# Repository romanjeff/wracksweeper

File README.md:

We are a Capstone team working with the Portland State University NEAR lab, under advisement by Dr. Martin
Siderius, and this repo is for the necessary files to implement or reference tha customizations we have done
to the AUV owned by the NEAR lab for academic research purposes. 

Our AUV is a Riptide Systems MP1 Mk.II, managed by a Beaglebone Black running MOOS-IvP (http://www.moos-ivp.org).

The project goal is to have full side-scan sonar capabilities, an emergency asset recovery tracking beacon, 
rechargeable power supply, and long-range wireless communications allowing us to check on the AUV's status,
give it new mission parameters, or toggle sonar functions without recovery and relaunch. Added features are
modular and removable to restore original state to the AUV.

Our sonar system is an Imagenex OEM side-scan module, and our wireless communications are done over LoRa at 
915 MHz using the Adafruit Feather M0 with HopeRF RFM95 transceiver modules. 

This project has been conducted at Portland State University by a team consisting of:

Drew Wendebrn, Matthew Moore, Patrick Hawn - Mechanical Engineering.  

Roman Minko, Adel Alkharraz - Sonar Interface Software.  

Colton Bruce - Beacon and RF link characterization.  

Jeff Roman - Communications Software.  

Jens Evens, Grace Semerdjian - Power System.  

http://www.wracksweeper.com

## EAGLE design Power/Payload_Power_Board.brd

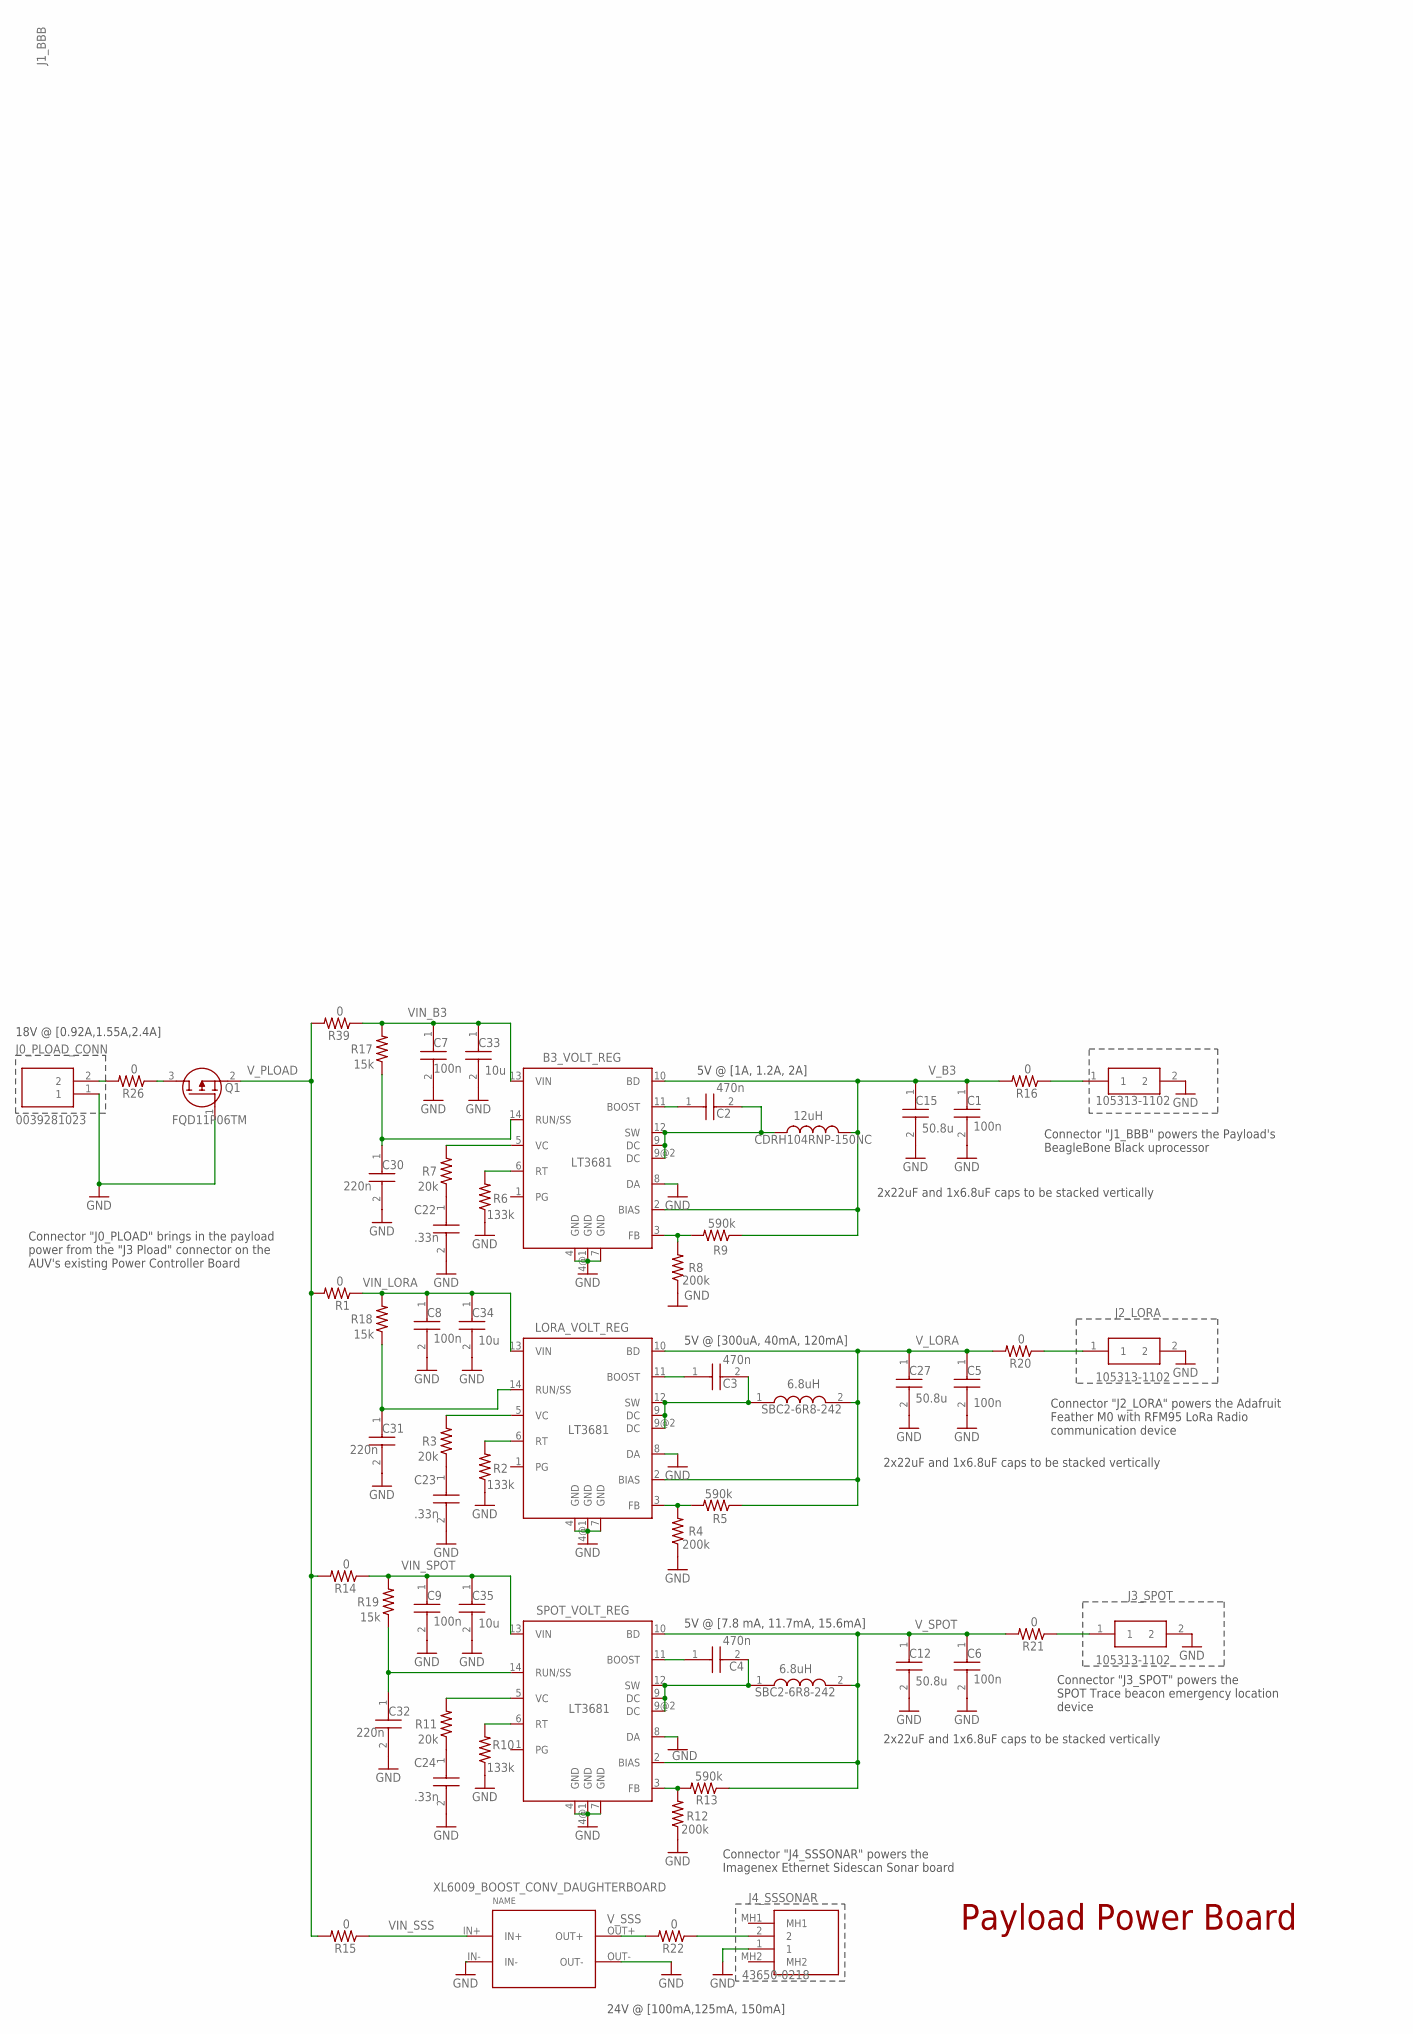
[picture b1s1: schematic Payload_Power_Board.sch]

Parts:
B3_VOLT_REG: LT3681; DFN14-4X3DE
C1, C5, C6, C7, C8, C9: 100n; CAPC1608X90N
C2, C3, C4: 470n; CAPC1608X90N
C12, C15, C27: 50.8u; CAPC3225X279N
C22, C23, C24: .33n; CAPC2012X140N
C30, C31, C32: 220n; CAPC2012X140N
C33, C34, C35: 10u; CAPC5750X279N
INDUCTOR_3: CDRH104RNP-150NC; INDPM102100X400N
J0_PLOAD_CONN: 0039281023; SHDR2W145P0X550_1X2_960X540X13
J1_BBB, J2_LORA, J3_SPOT: 105313-1102; 1053131102
J4_SSSONAR: 43650-0218; 436500218
L4, L5: SBC2-6R8-242; SBC26R8242
LORA_VOLT_REG: LT3681; DFN14-4X3DE
Q1: FQD11P06TM; DPAK3-CASE-369AS
R1, R14, R15, R16, R20, R21, R22, R26, R39: 0; 0207/2V; MPN RC0805FR-0710KL
R2, R6, R10: 133k; R0603
R3, R7, R11: 20k; R0603
R4, R8, R12: 200k; R0603
R5, R9, R13: 590k; R0603
R17, R18, R19: 15k; R0603
SPOT_VOLT_REG: LT3681; DFN14-4X3DE
XL6009_BOOST_CONV_DAUGHTERBOARD: XL6009; CP8-ADJ

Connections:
CBOOST_B3: B3_VOLT_REG.11 (BOOST), C2.1
CBOOST_LORA: C3.1, LORA_VOLT_REG.11 (BOOST)
CBOOST_SPOT: C4.1, SPOT_VOLT_REG.11 (BOOST)
FB_B3: B3_VOLT_REG.3 (FB), R8.2, R9.2
FB_LORA: LORA_VOLT_REG.3 (FB), R4.2, R5.2
FB_SPOT: R12.2, R13.2, SPOT_VOLT_REG.3 (FB)
GND: B3_VOLT_REG.4 (GND), B3_VOLT_REG.4@1 (GND), B3_VOLT_REG.7 (GND), B3_VOLT_REG.8 (DA), C1.2, C5.2, C6.2, C7.2, C8.2, C9.2, C12.2, C15.2, C22.2, C23.2, C24.2, C27.2, C30.2, C31.2, C32.2, C33.2, C34.2, C35.2, J0_PLOAD_CONN.1, J1_BBB.2, J2_LORA.2, J3_SPOT.2, J4_SSSONAR.1, LORA_VOLT_REG.4 (GND), LORA_VOLT_REG.4@1 (GND), LORA_VOLT_REG.7 (GND), LORA_VOLT_REG.8 (DA), Q1.1 (G), R2.1, R4.1, R6.1, R8.1, R10.1, R12.1, SPOT_VOLT_REG.4 (GND), SPOT_VOLT_REG.4@1 (GND), SPOT_VOLT_REG.7 (GND), SPOT_VOLT_REG.8 (DA), XL6009_BOOST_CONV_DAUGHTERBOARD.IN-, XL6009_BOOST_CONV_DAUGHTERBOARD.OUT-
unnamed: C22.1, R7.1
unnamed: C23.1, R3.1
unnamed: C24.1, R11.1
RT_B3: B3_VOLT_REG.6 (RT), R6.2
RT_LORA: LORA_VOLT_REG.6 (RT), R2.2
RT_SPOT: R10.2, SPOT_VOLT_REG.6 (RT)
RUN/SS_B3: B3_VOLT_REG.14 (RUN/SS), C30.1, R17.1
RUN/SS_LORA: C31.1, LORA_VOLT_REG.14 (RUN/SS), R18.1
RUN/SS_SPOT: C32.1, R19.1, SPOT_VOLT_REG.14 (RUN/SS)
SW_B3: B3_VOLT_REG.9 (DC), B3_VOLT_REG.9@2 (DC), B3_VOLT_REG.12 (SW), C2.2, INDUCTOR_3.1
SW_LORA: C3.2, L5.1, LORA_VOLT_REG.9 (DC), LORA_VOLT_REG.9@2 (DC), LORA_VOLT_REG.12 (SW)
SW_SPOT: C4.2, L4.1, SPOT_VOLT_REG.9 (DC), SPOT_VOLT_REG.9@2 (DC), SPOT_VOLT_REG.12 (SW)
VC_B3: B3_VOLT_REG.5 (VC), R7.2
VC_LORA: LORA_VOLT_REG.5 (VC), R3.2
VC_SPOT: R11.2, SPOT_VOLT_REG.5 (VC)
VIN_B3: B3_VOLT_REG.13 (VIN), C7.1, C33.1, R17.2, R39.1
VIN_LORA: C8.1, C34.1, LORA_VOLT_REG.13 (VIN), R1.1, R18.2
VIN_SPOT: C9.1, C35.1, R14.1, R19.2, SPOT_VOLT_REG.13 (VIN)
VIN_SSS: R15.1, XL6009_BOOST_CONV_DAUGHTERBOARD.IN+
V_B3: B3_VOLT_REG.2 (BIAS), B3_VOLT_REG.10 (BD), C1.1, C15.1, INDUCTOR_3.2, R9.1, R16.2
V_B31: J1_BBB.1, R16.1
V_LORA: C5.1, C27.1, L5.2, LORA_VOLT_REG.2 (BIAS), LORA_VOLT_REG.10 (BD), R5.1, R20.2
V_LORA1: J2_LORA.1, R20.1
V_PLOAD: Q1.2 (S), R1.2, R14.2, R15.2, R39.2
V_PLOAD0: Q1.3 (D), R26.1
V_PLOAD00: J0_PLOAD_CONN.2, R26.2
V_SPOT: C6.1, C12.1, L4.2, R13.1, R21.2, SPOT_VOLT_REG.2 (BIAS), SPOT_VOLT_REG.10 (BD)
V_SPOT1: J3_SPOT.1, R21.1
V_SSS: R22.2, XL6009_BOOST_CONV_DAUGHTERBOARD.OUT+
V_SSS1: J4_SSSONAR.2, R22.1

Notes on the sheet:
XL6009_BOOST_CONV_DAUGHTERBOARD
6.8uH
12uH
Payload Power Board
.33n
220n
10u
470n
50.8u
2x22uF and 1x6.8uF caps to be stacked vertically
18V @ [0.92A,1.55A,2.4A]
Connector "J1_BBB" powers the Payload's BeagleBone Black uprocessor
Connector "J2_LORA" powers the Adafruit Feather M0 with RFM95 LoRa Radio communication device
Connector "J3_SPOT" powers the SPOT Trace beacon emergency location device
Connector "J4_SSSONAR" powers the Imagenex Ethernet Sidescan Sonar board
5V @ [1A, 1.2A, 2A]
5V @ [300uA, 40mA, 120mA]
5V @ [7.8 mA, 11.7mA, 15.6mA]
24V @ [100mA,125mA, 150mA]
Connector "J0_PLOAD" brings in the payload power from the "J3 Pload" connector on the AUV's existing Power Controller Board

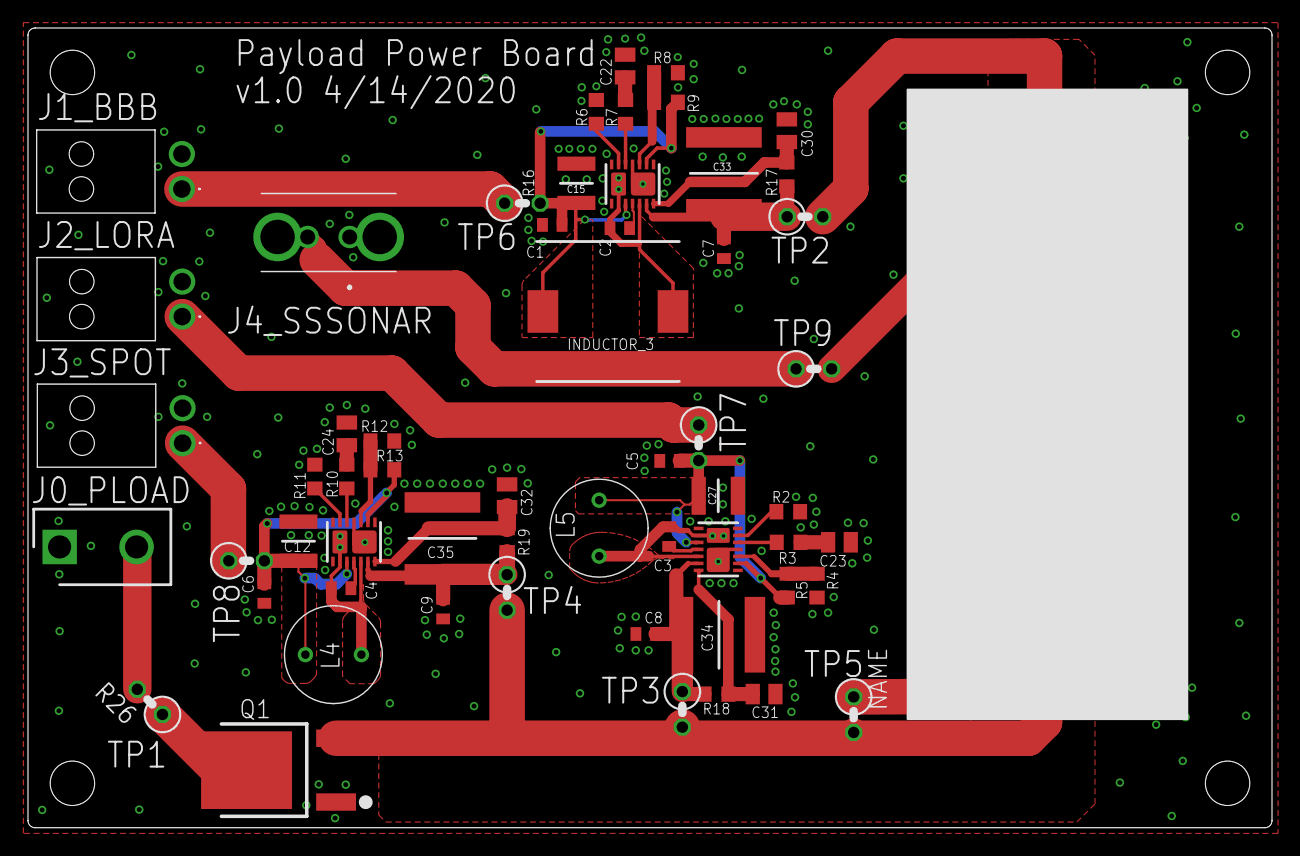
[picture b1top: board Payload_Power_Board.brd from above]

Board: 2 copper layers, 88.9 x 57.1 mm, 58 parts (0 on the bottom side), 37 nets.

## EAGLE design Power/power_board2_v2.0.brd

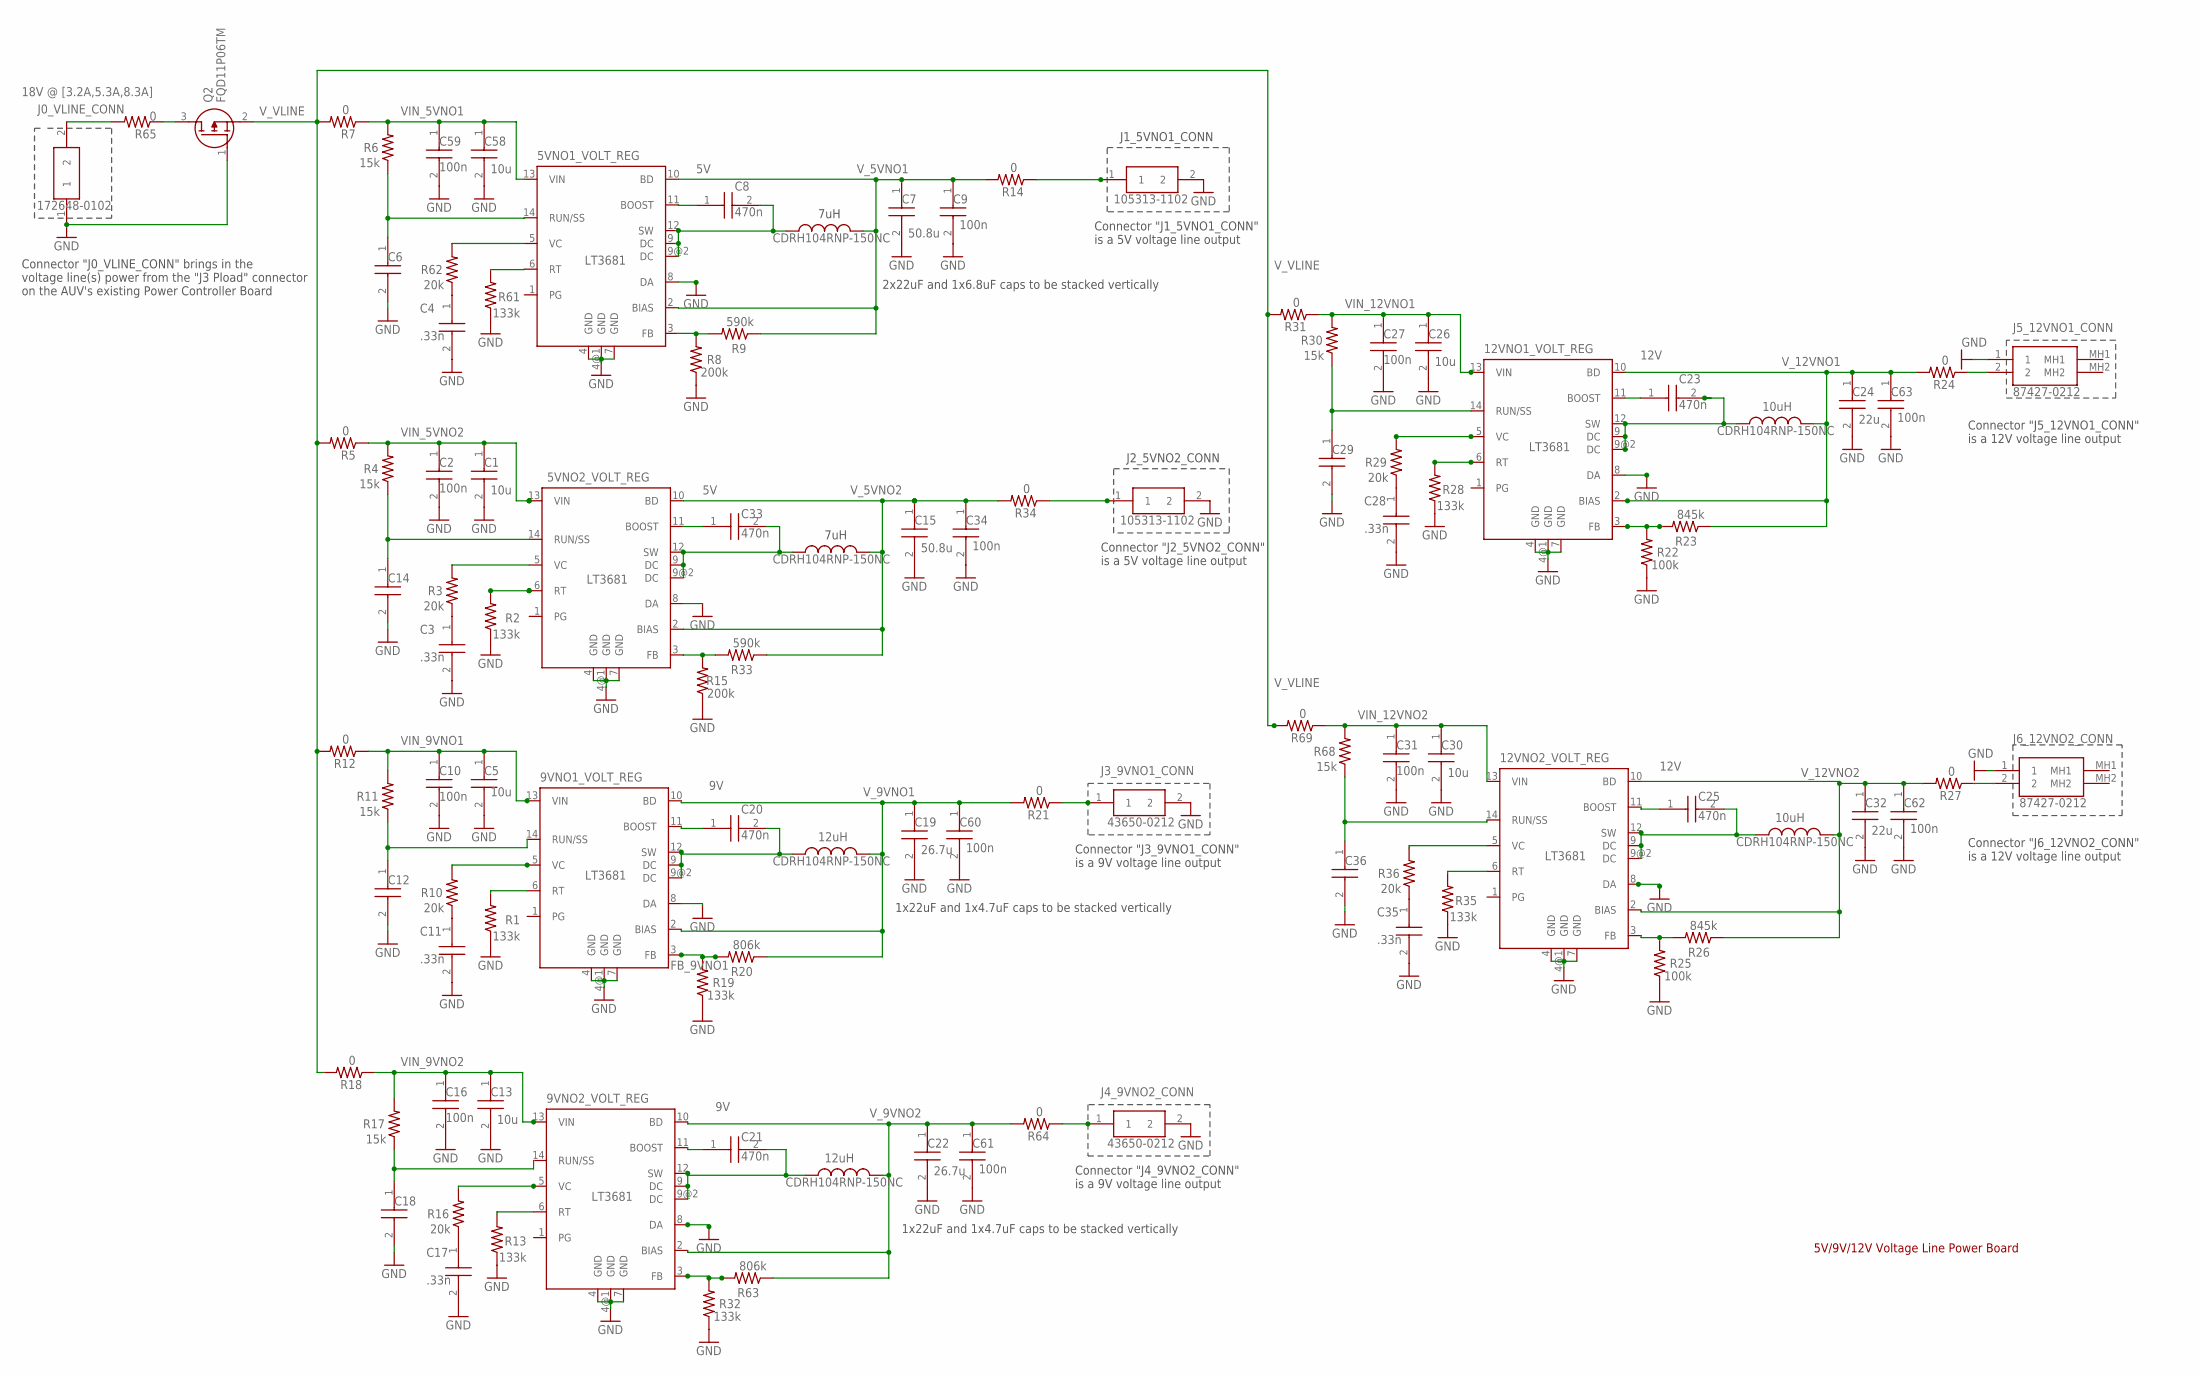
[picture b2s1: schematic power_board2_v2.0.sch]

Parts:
5VNO1_VOLT_REG, 5VNO2_VOLT_REG, 9VNO1_VOLT_REG, 9VNO2_VOLT_REG, 12VNO1_VOLT_REG, 12VNO2_VOLT_REG: LT3681; DFN14-4X3DE
C1, C5, C13, C26, C30, C58: 10u; CAPC5750X279N
C2, C9, C10, C16, C27, C31, C34, C59, C60, C61, C62, C63: 100n; CAPC1608X90N
C3, C4, C11, C17, C28, C35: .33n; CAPC2012X140N
C6, C12, C14, C18, C29, C36: 220n; CAPC2012X140N
C7, C15: 50.8u; CAPC3225X279N
C8, C20, C21, C23, C25, C33: 470n; CAPC1608X90N
C19, C22: 26.7u; CAPC3225X279N
C24, C32: 22u; CAPC3225X279N
INDUCTOR_2, INDUCTOR_4, INDUCTOR_5, INDUCTOR_6, INDUCTOR_7, INDUCTOR_8: CDRH104RNP-150NC; INDPM102100X400N
J0_VLINE_CONN: 172648-0102; 1726480102
J1_5VNO1_CONN, J2_5VNO2_CONN: 105313-1102; 1053131102
J3_9VNO1_CONN, J4_9VNO2_CONN: 43650-0212; 43650-0214
J5_12VNO1_CONN, J6_12VNO2_CONN: 87427-0212; 874270212
Q2: FQD11P06TM; DPAK3-CASE-369AS
R1, R2, R13, R19, R28, R32, R35, R61: 133k; R0603
R3, R10, R16, R29, R36, R62: 20k; R0603
R4, R6, R11, R17, R30, R68: 15k; R0603
R5, R7, R12, R14, R18, R21, R24, R27, R31, R34, R64, R65, R69: 0; 0207/2V; MPN RC0805FR-0710KL
R8, R15: 200k; R0603
R9, R33: 590k; R0603
R20, R63: 806k; R0603
R22, R25: 100k; R0603
R23, R26: 845k; R0603

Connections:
CBOOST_5VNO1: 5VNO1_VOLT_REG.11 (BOOST), C8.1
CBOOST_5VNO2: 5VNO2_VOLT_REG.11 (BOOST), C33.1
CBOOST_9VNO1: 9VNO1_VOLT_REG.11 (BOOST), C20.1
CBOOST_9VNO2: 9VNO2_VOLT_REG.11 (BOOST), C21.1
CBOOST_12VNO1: 12VNO1_VOLT_REG.11 (BOOST), C23.1
CBOOST_12VNO2: 12VNO2_VOLT_REG.11 (BOOST), C25.1
FB_5VNO1: 5VNO1_VOLT_REG.3 (FB), R8.2, R9.2
FB_5VNO2: 5VNO2_VOLT_REG.3 (FB), R15.2, R33.2
FB_9VNO1: 9VNO1_VOLT_REG.3 (FB), R19.2, R20.2
FB_9VNO2: 9VNO2_VOLT_REG.3 (FB), R32.2, R63.2
FB_12VNO1: 12VNO1_VOLT_REG.3 (FB), R22.2, R23.2
FB_12VNO2: 12VNO2_VOLT_REG.3 (FB), R25.2, R26.2
GND: 5VNO1_VOLT_REG.4 (GND), 5VNO1_VOLT_REG.4@1 (GND), 5VNO1_VOLT_REG.7 (GND), 5VNO1_VOLT_REG.8 (DA), 5VNO2_VOLT_REG.4 (GND), 5VNO2_VOLT_REG.4@1 (GND), 5VNO2_VOLT_REG.7 (GND), 5VNO2_VOLT_REG.8 (DA), 9VNO1_VOLT_REG.4 (GND), 9VNO1_VOLT_REG.4@1 (GND), 9VNO1_VOLT_REG.7 (GND), 9VNO1_VOLT_REG.8 (DA), 9VNO2_VOLT_REG.4 (GND), 9VNO2_VOLT_REG.4@1 (GND), 9VNO2_VOLT_REG.7 (GND), 9VNO2_VOLT_REG.8 (DA), 12VNO1_VOLT_REG.4 (GND), 12VNO1_VOLT_REG.4@1 (GND), 12VNO1_VOLT_REG.7 (GND), 12VNO1_VOLT_REG.8 (DA), 12VNO2_VOLT_REG.4 (GND), 12VNO2_VOLT_REG.4@1 (GND), 12VNO2_VOLT_REG.7 (GND), C1.2, C2.2, C3.2, C4.2, C5.2, C6.2, C7.2, C9.2, C10.2, C11.2, C12.2, C13.2, C14.2, C15.2, C16.2, C17.2, C18.2, C19.2, C22.2, C24.2, C26.2, C27.2, C28.2, C29.2, C30.2, C31.2, C32.2, C34.2, C35.2, C36.2, C58.2, C59.2, C60.2, C61.2, C62.2, C63.2, J0_VLINE_CONN.1, J1_5VNO1_CONN.2, J2_5VNO2_CONN.2, J3_9VNO1_CONN.2, J4_9VNO2_CONN.2, J5_12VNO1_CONN.1, J6_12VNO2_CONN.1, Q2.1 (G), R1.1, R2.1, R8.1, R13.1, R15.1, R19.1, R22.1, R25.1, R28.1, R32.1, R35.1, R61.1
unnamed: C4.1, R62.1
unnamed: C3.1, R3.1
unnamed: C11.1, R10.1
unnamed: C17.1, R16.1
unnamed: C28.1, R29.1
unnamed: C35.1, R36.1
RT_5VNO1: 5VNO1_VOLT_REG.6 (RT), R61.2
RT_5VNO2: 5VNO2_VOLT_REG.6 (RT), R2.2
RT_9VNO1: 9VNO1_VOLT_REG.6 (RT), R1.2
RT_9VNO2: 9VNO2_VOLT_REG.6 (RT), R13.2
RT_12VNO1: 12VNO1_VOLT_REG.6 (RT), R28.2
RT_12VNO2: 12VNO2_VOLT_REG.6 (RT), R35.2
RUN/SS_5VNO1: 5VNO1_VOLT_REG.14 (RUN/SS), C6.1, R6.1
RUN/SS_5VNO2: 5VNO2_VOLT_REG.14 (RUN/SS), C14.1, R4.1
RUN/SS_9VNO1: 9VNO1_VOLT_REG.14 (RUN/SS), C12.1, R11.1
RUN/SS_9VNO2: 9VNO2_VOLT_REG.14 (RUN/SS), C18.1, R17.1
RUN/SS_12VNO1: 12VNO1_VOLT_REG.14 (RUN/SS), C29.1, R30.1
RUN/SS_12VNO2: 12VNO2_VOLT_REG.14 (RUN/SS), C36.1, R68.1
SW_5VNO1: 5VNO1_VOLT_REG.9 (DC), 5VNO1_VOLT_REG.9@2 (DC), 5VNO1_VOLT_REG.12 (SW), C8.2, INDUCTOR_2.1
SW_5VNO2: 5VNO2_VOLT_REG.9 (DC), 5VNO2_VOLT_REG.9@2 (DC), 5VNO2_VOLT_REG.12 (SW), C33.2, INDUCTOR_4.1
SW_9VNO1: 9VNO1_VOLT_REG.9 (DC), 9VNO1_VOLT_REG.9@2 (DC), 9VNO1_VOLT_REG.12 (SW), C20.2, INDUCTOR_5.1
SW_9VNO2: 9VNO2_VOLT_REG.9 (DC), 9VNO2_VOLT_REG.9@2 (DC), 9VNO2_VOLT_REG.12 (SW), C21.2, INDUCTOR_6.1
SW_12VNO1: 12VNO1_VOLT_REG.9 (DC), 12VNO1_VOLT_REG.9@2 (DC), 12VNO1_VOLT_REG.12 (SW), C23.2, INDUCTOR_7.1
SW_12VNO2: 12VNO2_VOLT_REG.9 (DC), 12VNO2_VOLT_REG.9@2 (DC), 12VNO2_VOLT_REG.12 (SW), C25.2, INDUCTOR_8.1
VC_5VNO1: 5VNO1_VOLT_REG.5 (VC), R62.2
VC_5VNO2: 5VNO2_VOLT_REG.5 (VC), R3.2
VC_9VNO1: 9VNO1_VOLT_REG.5 (VC), R10.2
VC_9VNO2: 9VNO2_VOLT_REG.5 (VC), R16.2
VC_12VNO1: 12VNO1_VOLT_REG.5 (VC), R29.2
VC_12VNO2: 12VNO2_VOLT_REG.5 (VC), R36.2
VIN_5VNO1: 5VNO1_VOLT_REG.13 (VIN), C58.1, C59.1, R6.2, R7.1
VIN_5VNO2: 5VNO2_VOLT_REG.13 (VIN), C1.1, C2.1, R4.2, R5.1
VIN_9VNO1: 9VNO1_VOLT_REG.13 (VIN), C5.1, C10.1, R11.2, R12.1
VIN_9VNO2: 9VNO2_VOLT_REG.13 (VIN), C13.1, C16.1, R17.2, R18.1
VIN_12VNO1: 12VNO1_VOLT_REG.13 (VIN), C26.1, C27.1, R30.2, R31.1
VIN_12VNO2: 12VNO2_VOLT_REG.13 (VIN), C30.1, C31.1, R68.2, R69.1
V_5VNO1: 5VNO1_VOLT_REG.2 (BIAS), 5VNO1_VOLT_REG.10 (BD), C7.1, C9.1, INDUCTOR_2.2, R9.1, R14.2
V_5VNO1_0: J1_5VNO1_CONN.1, R14.1
V_5VNO2: 5VNO2_VOLT_REG.2 (BIAS), 5VNO2_VOLT_REG.10 (BD), C15.1, C34.1, INDUCTOR_4.2, R33.1, R34.2
V_5VNO2_0: J2_5VNO2_CONN.1, R34.1
V_9VNO1: 9VNO1_VOLT_REG.2 (BIAS), 9VNO1_VOLT_REG.10 (BD), C19.1, C60.1, INDUCTOR_5.2, R20.1, R21.2
V_9VNO1_0: J3_9VNO1_CONN.1, R21.1
V_9VNO2: 9VNO2_VOLT_REG.2 (BIAS), 9VNO2_VOLT_REG.10 (BD), C22.1, C61.1, INDUCTOR_6.2, R63.1, R64.2
V_9VNO2_0: J4_9VNO2_CONN.1, R64.1
V_12VNO1: 12VNO1_VOLT_REG.2 (BIAS), 12VNO1_VOLT_REG.10 (BD), C24.1, C63.1, INDUCTOR_7.2, R23.1, R24.2
V_12VNO1_0: J5_12VNO1_CONN.2, R24.1
V_12VNO2: 12VNO2_VOLT_REG.2 (BIAS), 12VNO2_VOLT_REG.10 (BD), C32.1, C62.1, INDUCTOR_8.2, R26.1, R27.2
V_12VNO2_0: J6_12VNO2_CONN.2, R27.1
V_VLINE: Q2.2 (S), R5.2, R7.2, R12.2, R18.2, R31.2, R69.2
V_VLINE00: J0_VLINE_CONN.2, R65.2
V_VLINE0: Q2.3 (D), R65.1

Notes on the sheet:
10u
.33n
50.8u
2x22uF and 1x6.8uF caps to be stacked vertically
J1_5VNO1_CONN
7uH
J2_5VNO2_CONN
12uH
Connector "J2_5VNO2_CONN" is a 5V voltage line output
Connector "J1_5VNO1_CONN" is a 5V voltage line output
18V @ [3.2A,5.3A,8.3A]
Connector "J0_VLINE_CONN" brings in the voltage line(s) power from the "J3 Pload" connector on the AUV's existing Power Controller Board
26.7u
22u
1x22uF and 1x4.7uF caps to be stacked vertically
Connector "J3_9VNO1_CONN" is a 9V voltage line output
5V/9V/12V Voltage Line Power Board
10uH
Connector "J4_9VNO2_CONN" is a 9V voltage line output
12V
Connector "J5_12VNO1_CONN" is a 12V voltage line output
Connector "J6_12VNO2_CONN" is a 12V voltage line output

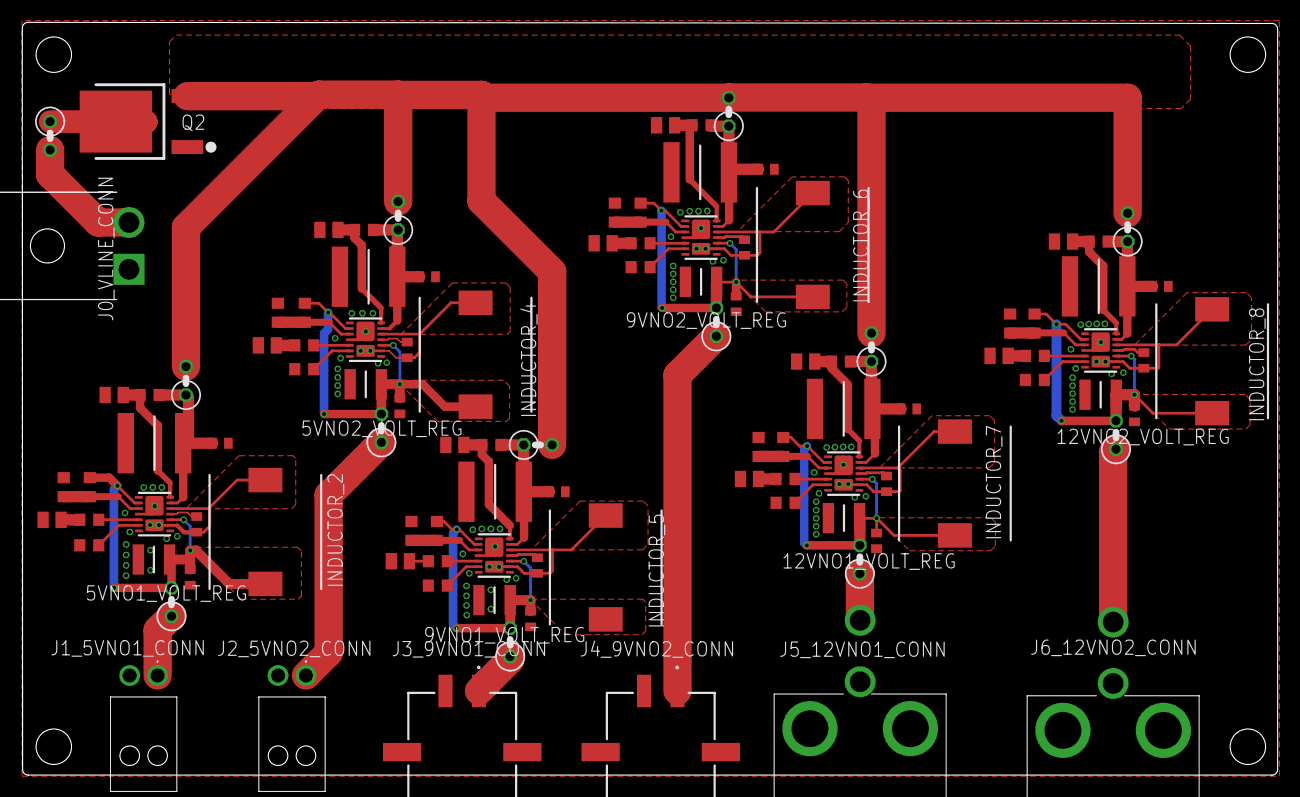
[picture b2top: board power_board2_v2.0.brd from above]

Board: 2 copper layers, 112.4 x 67.4 mm, 105 parts (0 on the bottom side), 64 nets.

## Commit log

2020-03-13 prepare the soil bed for planting of code.
2020-03-13 placeholders for folders
2020-03-24 march_23_20_power_board1_v2.0.sch
2020-03-24 peripheral_devices_power_controller_board_v1.0.sch
2020-03-27 Sonar code
2020-03-31 Skeleton of UART process daemon
2020-03-31 march_30_20_power_board2_v1.0.sch
2020-03-31 power_board2_v1.0.sch
2020-04-02 Cleaned up the Payload Power Board sch and brd and am almost done with the Voltage Lines Board sch and brd
2020-04-08 Included larger size mounting holes on both .brd files, pretty much finished board 2 (haven't GND'ed yet, need a design review)
2020-04-08 cleaned arduino sketches, still in progress
2020-04-09 fixed bug which was adding unprintable characters to some serial input
2020-04-11 power system failure broadcast code module tested and integrated
2020-04-11 Changed datagrams to reliable with ack/CRC, 5 retries, 4 second timeout
2020-04-11 prevented buffer size problems I hope
2020-04-14 Minor bug fixes
2020-04-15 Redesigned layout to fit in AUV. Changed 18V and 24V to mini and micro (also vertical), tucked connectors into board, all wrapped up
2020-04-15 Forgot to add names to components (helpful for assembly)
2020-04-22 LoRa settings toggle code added and tested.
2020-04-23 added packet timer, cleaned and consolidated code a bit.
2020-04-27 Boards being made at OSHPark were wrt these files
2020-04-29 Create a
2020-04-29 Rename Sonar/.gitkeep3 to Sonar/Linux Code/.gitkeep3
2020-04-29 Rename Sonar/Makefile to Sonar/Linux Code/Makefile
2020-04-29 Added Linux Code
2020-04-29 Added temp files
2020-04-29 Added code and dependencies
2020-04-29 Added Linux packet captures
2020-04-29 Create LICENSE
2020-04-29 Basic Info
2020-04-29 Added Windows packet captures
2020-04-30 finished Arduino sketches pending reorganizing them for clarity
2020-05-01 added some fine tuning to arduino code to enable handshake-free settings change
2020-05-02 Started BBB-side serial code
2020-05-06 Create test
2020-05-06 done
2020-05-06 working code - still need some code cleanup
2020-05-06 working code - still needs cleanup
2020-05-13 final version of code
2020-05-17 python UART daemon, some touchup on arduino code
2020-05-17 it's a daemon now
2020-05-18 fixed -changemode method, made backspace-safe
2020-05-21 Addressed datagram, consolidated into single sketch
2020-05-24 Improved documentation on these two files
2020-05-28 Added code for future improvement
    For implementing beyond a single command line with user prompts and all that good stuff
2020-05-28 Future code
2020-05-28 Future code
    For implementing beyond a single command line with user prompts and all that good stuff
2020-05-28 Update Makefile
2020-05-28 Added script to run program
2020-05-30 Doc/Setup Guide For Comms Code
2020-05-31 changed user input from 32 bits to 8 bits
2020-05-31 Rename waves.sh to waves
2020-05-31 update header file
2020-05-31 updated code to be compatible with script arguments
2020-05-31 updated script to accept necessary arguments
2020-06-01 added manual for running the software
2020-06-01 delete README.md
    Refer to the Sonar Software Manual on how to execute the program
2020-06-01 added design doc
2020-06-04 Updated the expected input voltage range
2020-11-12 Post Processing
    Created a folder for post processing and a inserted a livescript for processing alog files.
2020-12-03 Update alogProcessor.mlx
    Updated with the objective and description of the script.
    Defined the desired variables.
    Automated the retrieval process for fetching variables for a given mission.
    Automated combining of GPS time into a single matrix
    Automated combining of NAV LAT/LONG into a single matrix.
    Working on combining GPS time with NAV LAT/LONG data.
2020-12-03 Update alogProcessor.mlx
    Doing a thing to size up and match data sets.
2020-12-07 Data sync and plotting.
    Automatic rebuilding of GPS time without gaps in seconds, same for NAV lat/long. Filled gaps, lined up data between GPS and NAV. Beginning of plotting - working on a gradient now.
2020-12-07 Testing fancy color stuff for plot.
    Needs work.
2020-12-08 small plot update
    nothing important really.
2020-12-11 Description updates
    Nothing special
2020-12-11 added klog folder
    added klog folder
2020-12-30 Cleanup
    Excludes superfluous data restricted to sample data and outputs.
2020-12-30 Alexs parser
    Includes Alex Higgen's parser and some sample data
2021-03-05 Post Processing is now Operations
    It's been a while since I've updated, but the matlab script has changed a little to be more robust and to include a plot that once perfected will have lat/long, depth, desired depth, and altitude.
2021-03-05 Small changes to alogProcessor
2021-03-05 small updates and sample files
2021-03-09 small inline description updates
2021-03-30 tweaks
2021-05-21 Folder structure
    It's nothing really.
